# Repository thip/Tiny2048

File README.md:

# Tiny2048

A custom ESP32 dev board with a built in 4x4 RGB LED Matrix and accelerometer.

Built to run an RGB version of 2048 - a simple but addictive game where you try to add up to 2048 by combining matching numbers on sliding tiles. 

Read more about the project at [https://hackaday.io/project/197115-tiny2048](https://hackaday.io/project/197115-tiny2048)

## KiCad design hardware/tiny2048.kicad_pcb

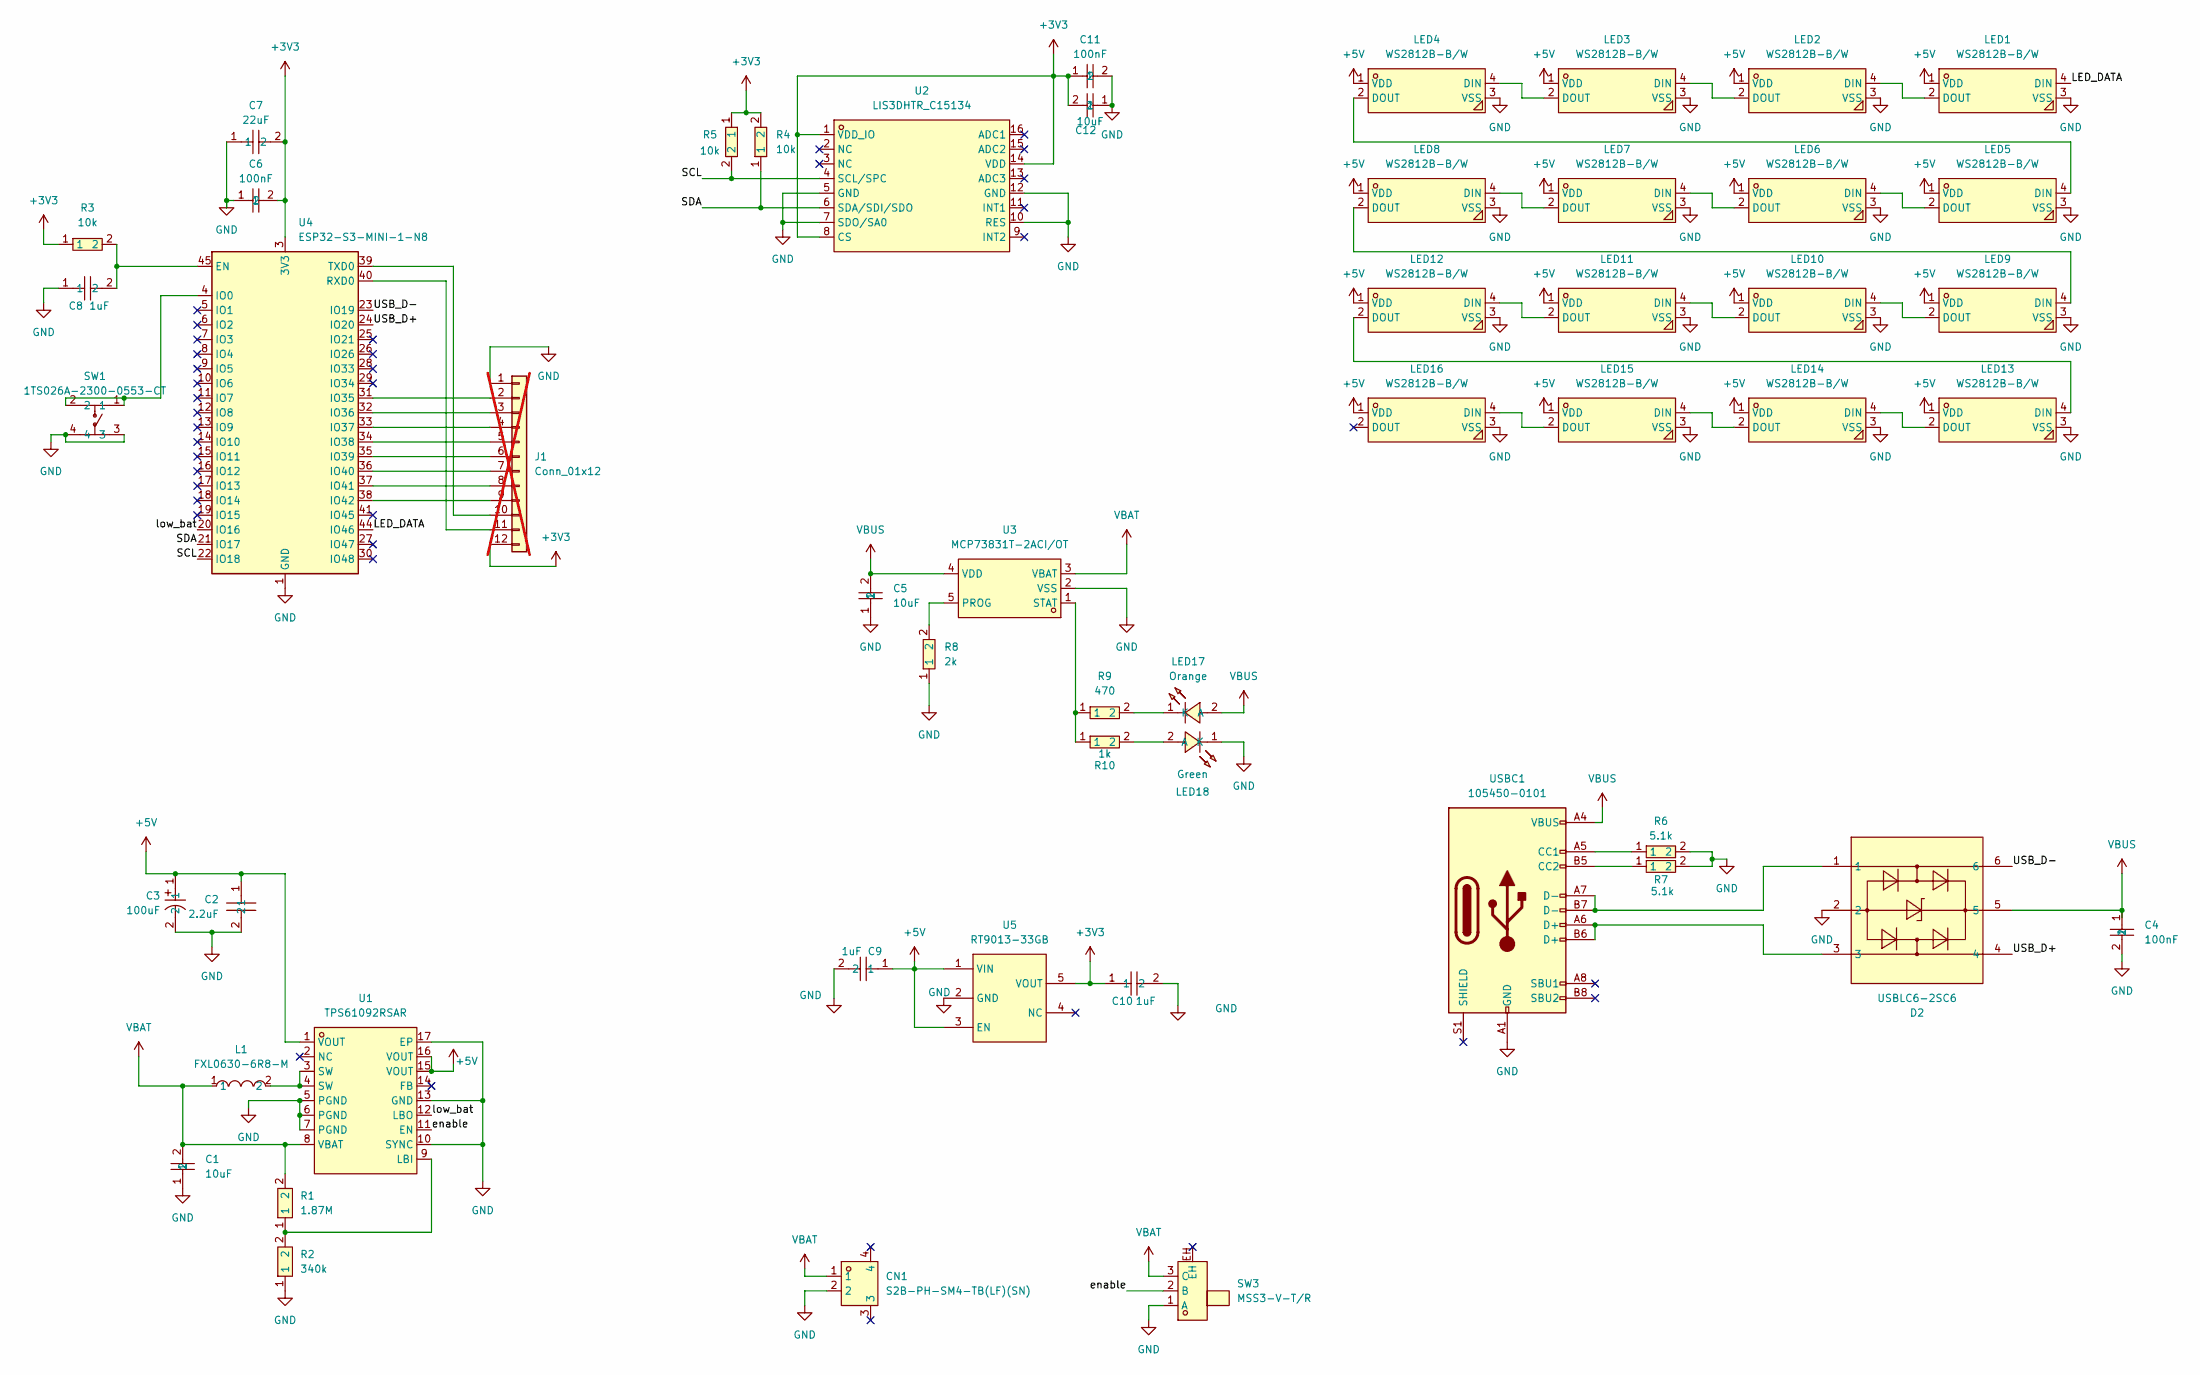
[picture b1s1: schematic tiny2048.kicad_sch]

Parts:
C1, C5, C12: 10uF; C0402; LCSC Part C15525
C2: 2.2uF; C0402; LCSC Part C12530
C3: 100uF; CAP-SMD_L7.3-W4.3-FD; LCSC Part C215892
C4, C6, C11: 100nF; C0402; LCSC Part C1525
C7: 22uF; C0603; LCSC Part C59461
C8, C9, C10: 1uF; C0603; LCSC Part C15849
CN1: S2B-PH-SM4-TB(LF)(SN); CONN-SMD_P2.00_S2B-PH-SM4-TB-LF-SN; LCSC Part C295747
D2: USBLC6-2SC6; SOT-23-6_L2.9-W1.6-P0.95-LS2.8-BL; LCSC Part C7519
J1: Conn_01x12; PinHeader_1x12_P2.54mm_Vertical; not fitted
L1: FXL0630-6R8-M; IND-SMD_L7.0-W6.6; LCSC Part C167221
LED1, LED2, LED3, LED4, LED5, LED6, LED7, LED8, LED9, LED10, LED11, LED12, LED13, LED14, LED15, LED16: WS2812B-B/W; LED-SMD_4P-L5.0-W5.0-TL_WS2812B-B; LCSC Part C2761795
LED17: Orange; LED0402-RD_ORANGE; LCSC Part C965791
LED18: Green; LED0402-RD_BLUE; LCSC Part C965797
R1: 1.87M; R0402; LCSC Part C368349
R2: 340k; R0402; LCSC Part C409910
R3, R4, R5: 10k; R0402; LCSC Part C25744
R6, R7: 5.1k; R0402; LCSC Part C25905
R8: 2k; R0402; LCSC Part C4109
R9: 470; R0402; LCSC Part C25117
R10: 1k; R0402; LCSC Part C11702
SW1: 1TS026A-2300-0553-CT; SW-SMD_4P-L2.6-W1.6-P0.75-LS3.0; LCSC Part C913791
SW3: MSS3-V-T/R; SW-SMD_MSS3-V-T-R; LCSC Part C495932
U1: TPS61092RSAR; QFN-16_L4.0-W4.0-P0.65-BL-EP2.7-1; LCSC Part C2878944
U2: LIS3DHTR_C15134; LGA-16_L3.0-W3.0-P0.50-TL; LCSC Part C15134
U3: MCP73831T-2ACI/OT; SOT-23-5_L3.0-W1.7-P0.95-LS2.8-BL; LCSC Part C424093
U4: ESP32-S3-MINI-1-N8; ESP32-S2-MINI-1; LCSC Part C2913206
U5: RT9013-33GB; SOT-23-5_L3.0-W1.7-P0.95-LS2.8-BL; LCSC Part C47773
USBC1: 105450-0101; USB_C_Receptacle_HCTL_HC-TYPE-C-16P-01A; LCSC Part C2894897

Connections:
+3V3: C6.2, C7.2, C10.1, C11.1, C12.2, J1.12, R3.1, R4.2, R5.1, U2.1 (VDD_IO), U2.8 (CS), U2.14 (VDD), U4.3 (3V3), U5.5 (VOUT)
+5V: C2.1, C3.1, C9.1, LED1.1 (VDD), LED2.1 (VDD), LED3.1 (VDD), LED4.1 (VDD), LED5.1 (VDD), LED6.1 (VDD), LED7.1 (VDD), LED8.1 (VDD), LED9.1 (VDD), LED10.1 (VDD), LED11.1 (VDD), LED12.1 (VDD), LED13.1 (VDD), LED14.1 (VDD), LED15.1 (VDD), LED16.1 (VDD), U1.1 (VOUT), U1.15 (VOUT), U1.16 (VOUT), U5.1 (VIN), U5.3 (EN)
/LED_DATA: LED1.4 (DIN), U4.44 (IO46)
/SCL: R5.2, U2.4 (SCL/SPC), U4.22 (IO18)
/SDA: R4.1, U2.6 (SDA/SDI/SDO), U4.21 (IO17)
/USB_D+: D2.4, U4.24 (IO20)
/USB_D-: D2.6, U4.23 (IO19)
/enable: SW3.2 (B), U1.11 (EN)
/low_bat: U1.12 (LBO), U4.20 (IO16)
GND: C1.1, C2.2, C3.2, C4.2, C5.1, C6.1, C7.1, C8.1, C9.2, C10.2, C11.2, C12.1, CN1.2, D2.2, J1.1, LED1.3 (VSS), LED2.3 (VSS), LED3.3 (VSS), LED4.3 (VSS), LED5.3 (VSS), LED6.3 (VSS), LED7.3 (VSS), LED8.3 (VSS), LED9.3 (VSS), LED10.3 (VSS), LED11.3 (VSS), LED12.3 (VSS), LED13.3 (VSS), LED14.3 (VSS), LED15.3 (VSS), LED16.3 (VSS), LED18.1 (K), R2.1, R6.2, R7.2, R8.1, SW1.3, SW1.4, SW3.1 (A), U1.5 (PGND), U1.6 (PGND), U1.7 (PGND), U1.10 (SYNC), U1.13 (GND), U1.17 (EP), U2.5 (GND), U2.7 (SDO/SA0), U2.10 (RES), U2.12 (GND), U3.2 (VSS), U4.1 (GND), U4.2 (GND), U4.42 (GND), U4.43 (GND), U4.46 (GND), U4.47 (GND), U4.48 (GND), U4.49 (GND), U4.50 (GND), U4.51 (GND), U4.52 (GND), U4.53 (GND), U4.54 (GND), U4.55 (GND), U4.56 (GND), U4.57 (GND), U4.58 (GND), U4.59 (GND), U4.60 (GND), U4.61 (GND), U4.62 (GND), U4.63 (GND), U4.64 (GND), U4.65 (GND), U5.2 (GND), USBC1.A1 (GND), USBC1.A12 (GND), USBC1.B1 (GND), USBC1.B12 (GND)
unnamed: D2.1, USBC1.A7 (D-), USBC1.B7 (D-)
unnamed: D2.3, USBC1.A6 (D+), USBC1.B6 (D+)
unnamed: J1.2, U4.31 (IO35)
unnamed: J1.3, U4.32 (IO36)
unnamed: J1.4, U4.33 (IO37)
unnamed: J1.5, U4.34 (IO38)
unnamed: J1.6, U4.35 (IO39)
unnamed: J1.7, U4.36 (IO40)
unnamed: J1.8, U4.37 (IO41)
unnamed: J1.9, U4.38 (IO42)
unnamed: J1.10, U4.39 (TXD0)
unnamed: J1.11, U4.40 (RXD0)
unnamed: L1.2, U1.3 (SW), U1.4 (SW)
unnamed: LED1.2 (DOUT), LED2.4 (DIN)
unnamed: LED2.2 (DOUT), LED3.4 (DIN)
unnamed: LED3.2 (DOUT), LED4.4 (DIN)
unnamed: LED4.2 (DOUT), LED5.4 (DIN)
unnamed: LED5.2 (DOUT), LED6.4 (DIN)
unnamed: LED6.2 (DOUT), LED7.4 (DIN)
unnamed: LED7.2 (DOUT), LED8.4 (DIN)
unnamed: LED8.2 (DOUT), LED9.4 (DIN)
unnamed: LED9.2 (DOUT), LED10.4 (DIN)
unnamed: LED10.2 (DOUT), LED11.4 (DIN)
unnamed: LED11.2 (DOUT), LED12.4 (DIN)
unnamed: LED12.2 (DOUT), LED13.4 (DIN)
unnamed: LED13.2 (DOUT), LED14.4 (DIN)
unnamed: LED14.2 (DOUT), LED15.4 (DIN)
unnamed: LED15.2 (DOUT), LED16.4 (DIN)
unnamed: LED17.1 (K), R9.2
unnamed: LED18.2 (A), R10.2
unnamed: R1.1, R2.2, U1.9 (LBI)
unnamed: R8.2, U3.5 (PROG)
unnamed: R9.1, R10.1, U3.1 (STAT)
unnamed: C8.2, R3.2, U4.45 (EN)
unnamed: SW1.1, SW1.2, U4.4 (IO0)
unnamed: R6.1, USBC1.A5 (CC1)
unnamed: R7.1, USBC1.B5 (CC2)
VBAT: C1.2, CN1.1, L1.1, R1.2, SW3.3 (C), U1.8 (VBAT), U3.3 (VBAT)
VBUS: C4.1, C5.2, D2.5, LED17.2 (A), U3.4 (VDD), USBC1.A4 (VBUS), USBC1.A9 (VBUS), USBC1.B4 (VBUS), USBC1.B9 (VBUS)

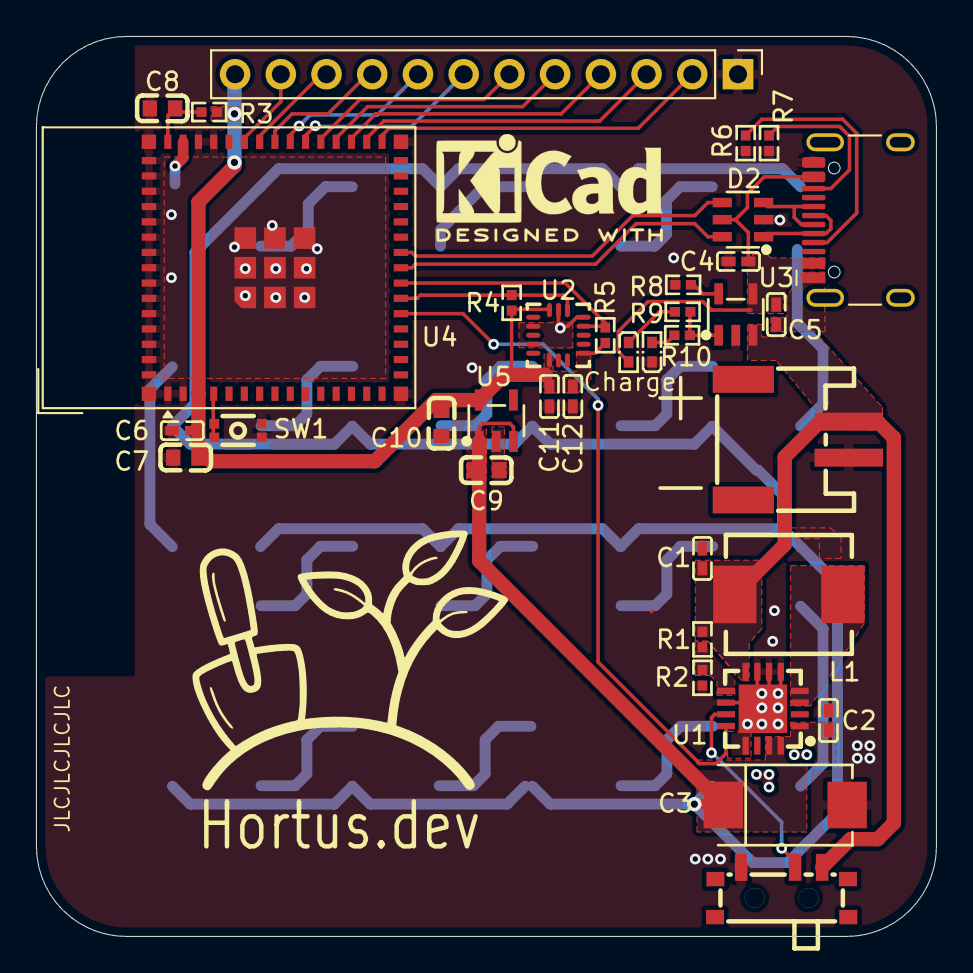
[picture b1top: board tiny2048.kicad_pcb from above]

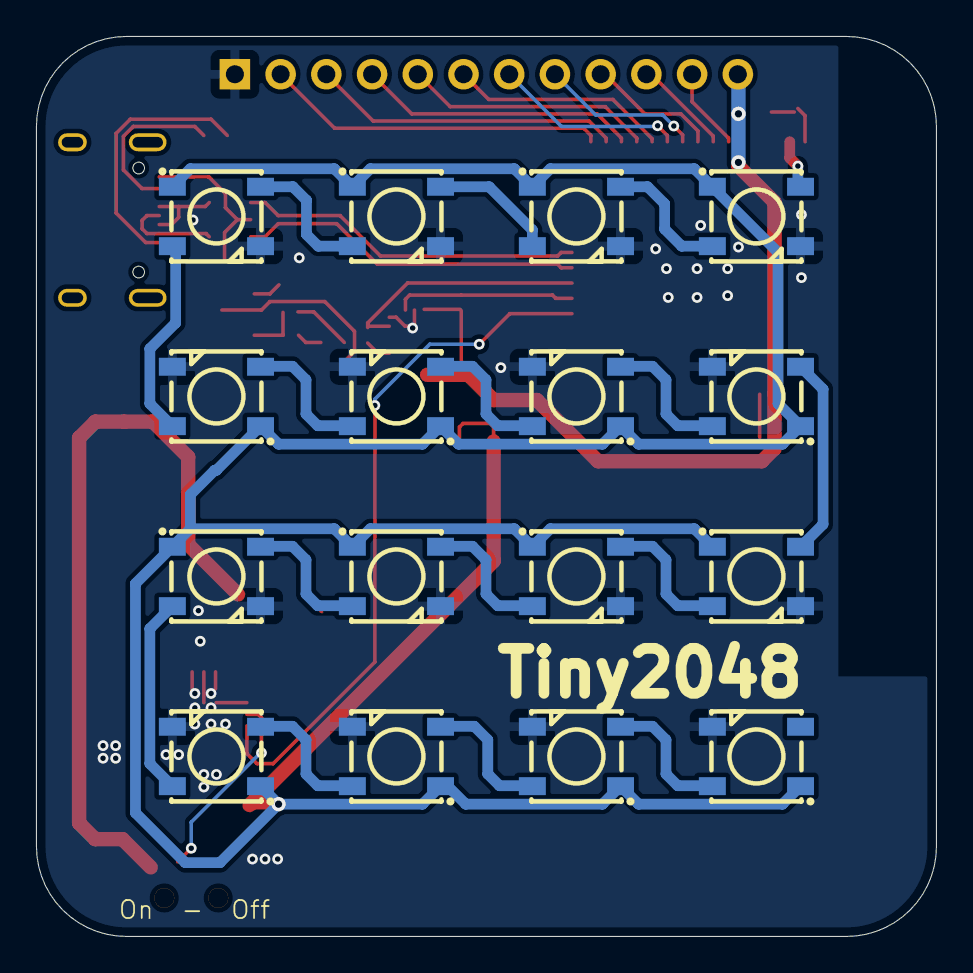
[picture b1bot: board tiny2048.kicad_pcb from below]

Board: 2 copper layers, 50.0 x 50.0 mm, 52 parts (16 on the bottom side), 49 nets.

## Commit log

2024-08-15 init
2024-10-18 refactor movement code and bring back animations
2024-10-18 add game loss state
2024-10-18 Add game won sequence
